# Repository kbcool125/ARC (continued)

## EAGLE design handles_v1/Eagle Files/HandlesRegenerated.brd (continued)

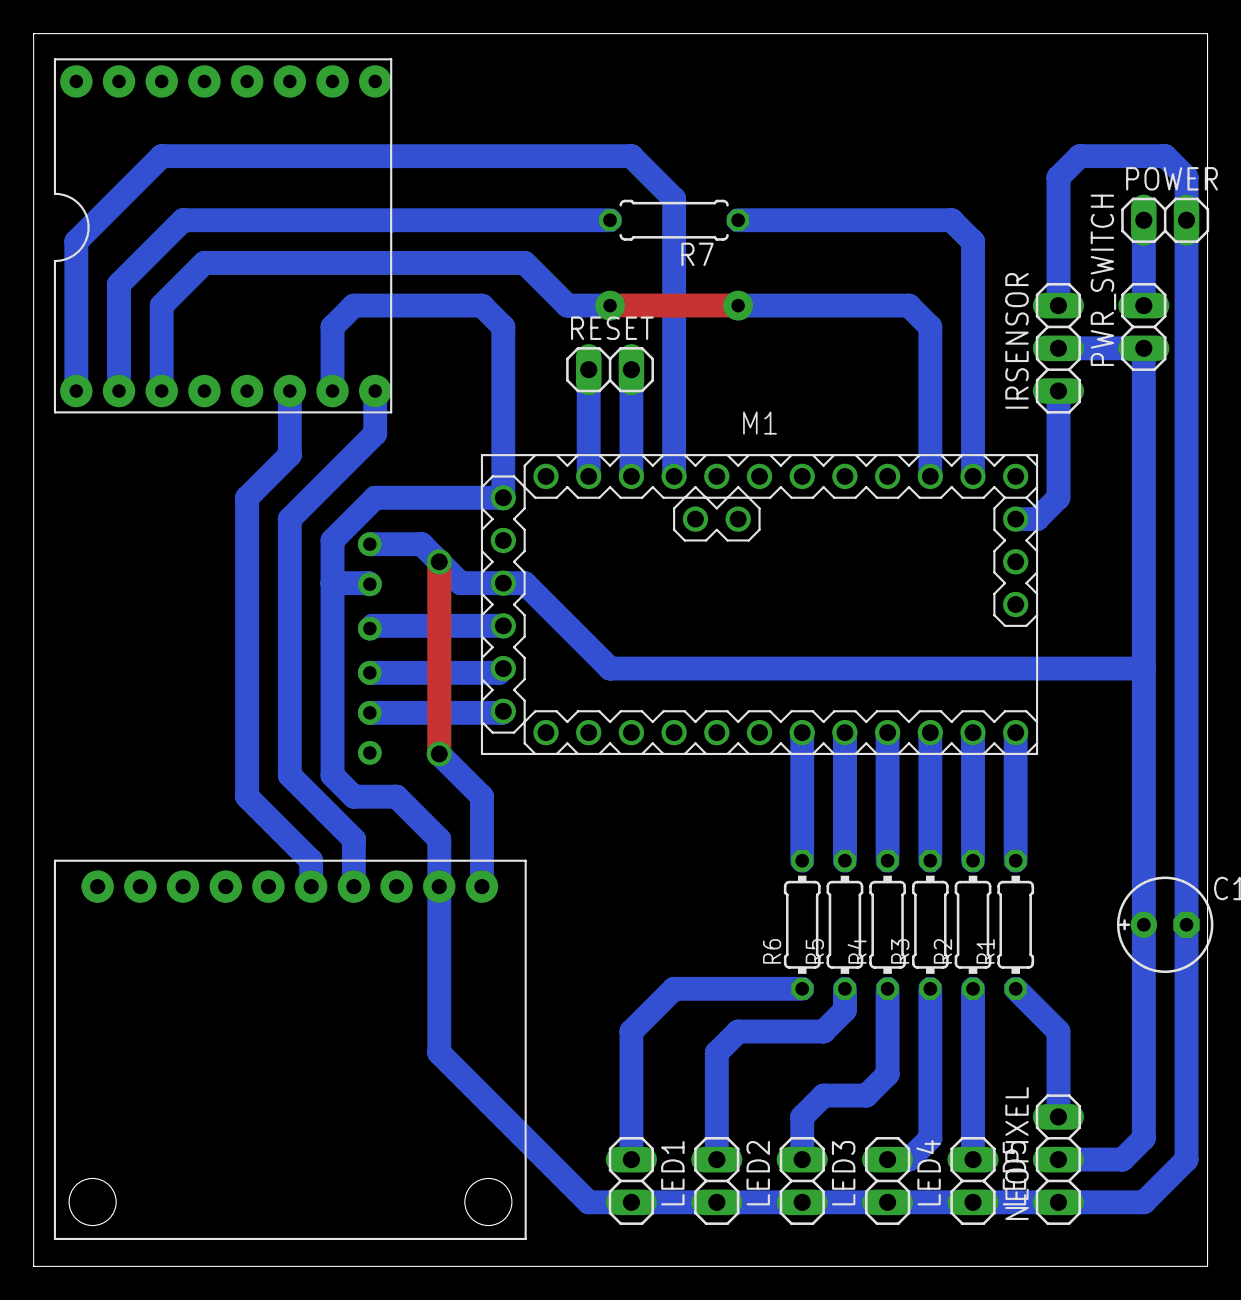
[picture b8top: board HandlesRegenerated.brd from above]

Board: 2 copper layers, 69.8 x 73.3 mm, 22 parts (1 on the bottom side), 27 nets.

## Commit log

2018-04-08 Added some arc project files
2018-04-08 Added more ARC related files
2018-04-08 Added yet more arc files
2018-04-08 removed cad files
